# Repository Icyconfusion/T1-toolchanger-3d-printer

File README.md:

# T1-toolchanger-3d-printer
A toolchanger 3d printer with large format build size and multiple tools for quick, easy multi-material printing that uses marlin as the firmware.

**Note to reviewer:** Since submitting project for review I have updated the BOM (haven't changed products, just updated the prices). The new bom is more than what was in the review, but I have multiple discounts and coupons (that I have also tested) which bring it back down to what I mentioned in review. Thank you :) Also, in regards to firmware, the entire marlin zip folder (must be a zip) is in the firmware folder, but I have copied all files that have been edited and/or relevant (e.g config and ino files) as well into the firmware folder for the reviewer to view. I was instructed to do it this way by other reviewers in similar projects. Thanks.

I made this project as I had been looking to make a 3d printer. I wanted to be able to print in different colours, without the added cost of AMS systems. It was also a good opportunity to learn about using programs like fusion and Kicad, which I have limited experience with, as well as learning about electronic components. I created this project without a guide, using my own ideas to combat problems, with some inspiration from existing products e.g using linear rods.

Note: The assembly files are too large to upload to Github directly. Instead I have put the assembly .step file and .f3z file into a zipped folder named: Printer assembly.zip 

I have also uploaded the same step file as a zipped folder called printer assembly Step.zip, and an STL file called printer assembly STL.zip, just to be sure.

The printer uses a swappable hotend mechanism to dock tools, removing the need to purge filament as in other multi-material systems. The idle toolheads sit on an aluminium extrusion. The X carriage, supported by a V slot extrusion, moves in and attaches to the toolhead, using kinematic couplings for repeatability. A magnetic pogo connector transfers power for the heter and thermistor.

Toolhead:

# **Assembly**

The printer assembly is made by aluminium extrusions forming a cube, with corner connectors for mounting.

To support the Y axis, V slot 2020 aluminium extrusions are used as rails holding a gantry, which in turn supports the X axis.
The Y axis is made up of two carriages, one either side of the X gantry. Each Y carriage uses a gantry plate with wheels to slide along the extrusions, making the Y motion. One carriage is an idler, which the belt loops around a pulley. The other carriage is the stepper motor carriage, which uses a Nema 17 motor to drive the X axis belt. Both carriages hold 90 degree connectors supporting the X extrusion.
Idler:

Stepper carriage:

The X carriage is made of two parts: the main carriage, and the toolhead. The main carriage holds the fan and the extruder stepper motor. When the carriage comes into dock, a fixed arm pushes the extruder idle arm to the side. The filament slides into the extruder,and when docking is complete, the spring loaded, idle arm pushes back into the filament, creating good tension. 

The fan is a 4010 fan, which sits to the side and blows cool air through the heatsink fins and also onto the part/top layer. 

The belt post is located behind the carriage.

The carriage sid of the coupling contains the 6mm smooth rods of the kinematic coupling. This is printed in two pieces, so that the rods can be put into grooves before the 'lid' of the coupling closes through screws. The pogo connector is also housed here.

The toolhead uses steel balls to push into the kinematic coupling. The male side of the pogo connector is on the toolhead.

The hotend mounts to the two holes in the middle.

The Z axis involves the motion of the bed up and down. Originally, I had planned to move the hotend throughout all 3 axis, and the bed was fixed. I encountered many issues with reliably and consistently achieving motion of the hotend without the risk of flexing, so I pivoted to a bed Z axis. A leadscrew and two 8mm linear rods are used on each side, connected to an aluminium profile by a nut block and 3d printed clamps.

The bed frame is a square made of aluminium extrusions, held together by 90 degree corner connectors. The 6mm aluminium print bed sits on top of that, threaded into T nuts in the profiles.

Toolchanging mechanism. Tools are held on the toolchanger rack, installed with T nuts on an aluminium profile. L shaped hooks hold the tools in place, using knobs on the tools.Wwhen the tool slides in sideways, the knob/tool will be separated from the carriage by the hook Then the carriage will move backwards, detaching the magnets in the connectors, and pulling the tool off the rack. To attach, it simply presses the carriage onto the tool, pushes it back and slides out. The magnets used in the connector and the balls should be enough to hold the tool in place, but in the event it is not, I can use print in place function in slicers to add in even stronger magnets in the centre (only if current magnet setup isn't strong enough - unlikely).

# **Electronics**

The printer uses a PCB motherboard to mount components including the MCU (Mega 2560), stepper drivers, LCD headers, and heater terminals. I decided on a 24v power supply as it was compatible with my heater. To give power to the PCB, I used a meanwell 24v 360W power supply.

This connects through wires to screw terminals on the board, which then distribute power across the PCB. Because of the power requirements, I decided to use a 4 layer PCB as I couldn't route signal traces through the power and GND traces. Using a 4 layer PCB is necessary to the peojwct due to the power layout of drivers, making signal traces impossible without a 3rd and 4th layer. The top and bottom layers of the PCB are the power layers. Power runs from the PSU input to the heater screw terminal, and throughout the board. It is converted to 5v through a buck converter. The Hotend heater is powered through a screw terminal, and controlled by the mosfet next to its terminal. The hotend fan is controlled by a header, it is in an always on state.

The signal traces from the drivers, limit switches, thermistor and LCD are on the second and third layers.

The MCU is a mega 2560. I chose this because of its large availability of pins, enabling future upgrades and fitting all components. The stepper drivers are A4988s, which have microstepping up to 1/16. All microstep pins are connected to 5v, making the configuration 1/16. The limit switches, thermistor and lcd connect to headers.

The power for the stepper drivers is 24v. To reduce the effect of spikes, a small 100nf capacitor is used between the 24v and gnd supply of each driver. For larger spikes, a 100 uF capacitor is also placed between 24v and gnd of each driver.

The LCD is the main user interface of the printer. I am using the BIGTREETECH TFT35 V3.0 Touch Screen from BigTreeTech which has wifi capability and is 3.5". I chose this LCD as it only uses 2 pins on the MCU (TX and RX), has an SD card, and is touchscreen. It is possible to mount the LCD separately to the motherboard, and run a cable between the two, enabling you to set it up however you like. LCD Header:

The Motherboard and PSU are not fixed components to the printer and can be placed wherever suitable as long as cabling reaches. (I already have a case at home for my pcb from older projects).

### Schematic

# **Firmware**

The printer uses the latest version of marlin firmware, which enables the use of G-code. The general firmware of the printer is fairly standard and straightforward, as marlin is just configured to the printer dimensions and layout. The firmware has been edited to match the printer configuration with things like pin usage, limits, dimensions, and rough speeds/acceleration (these will require testing following assembly).

However, the printer being a toolchanger introduces a unique element to the firmware in the connection and preparation of multiple toolheads. To simplify firmware and general electronics, I decided on having 'hot-swappable' toolheads that connect through pogo connectors. Because of this, the firmware views it as one hotend when it comes to heating the temperature monitoring. In this aspect, the printer appears as standard. To facilitate toolchanges though, special G-code is required to move the carriage into specific positions. This is most effectively achieved through pre and post g-code in the slicer per tool. The main idea of the toolchange G-code is that the empty carriage moves into alignment with the passive tool, moves forward to latch on, and then returns to the print area. When returning a tool to the standby dock, it is the same idea in reverse, where it moves into a specific position, pushes the tool into the dock, and returns to pick up another tool. This is the series of G-code to paste into the slicer pre and post processing:

Pre:

M1 X(Tool X value) Y440 F6000

M1 X(Tool X value) Y480 F2000

M1 X(Tool X value + 60) Y480 F2000

M1 X(Tool X value + 60) Y440 F2000

Post:

M1 X(Tool X value + 60) Y440 F6000

M1 X(Tool X value + 60) Y480 F2000

M1 X(Tool X value) Y480 F2000

M1 X(Tool X value) Y440 F1000

The X values are unique to each tool, as tools are docked in order across the X axis. Specific values will require precise tuning with manual adjustment following assembly to ensure correct alignment of the coupling, so values are not possible now, but the spacing between docks will be roughly 100mm.

Breaking down this G-code, the carriage moves into a position hovering off of the dock, in X alignment. The carriage then slowly pushes into the docked tool in the second G-code command. At this point, the kinematic coupling engages, ensuring alignment, and the magnetic clamp and pogo connectors attach, preparing the tool for printing. The third G-code command moves the carriage and new tool to the right, out of the dock, before returning to the print area with the fourth command. this process occurs in reverse for the docking of the tool/post G-code series.

# **BOM**
### CAD

| Quanity      | Name                     |  Picture    |
| -------------| -------------------------|-----------  |
| 1            | New X carriage               |
| 1 (per tool) | Toolhead                 |
| 4            | Z axis bearing clamp     |
| 2            | Z stepper bracket        |
| 4            | Z rod holder             |
| 2       | Nema 17 parallel mount| 
|4 | plain limit switch bracket| 
|4| z rod top bracket|
|1| toolchanger rack| 

### PCB
4 layer PCB that is 230x135mm:

Layers 1 and 4 make up the power layers, 24v (a small bit of 5v) and GND. This was a requirement due to the large power draw of the machine, requiring thick traces that took up a lot of room. I tried routing the pcb using only 2 layers, but this was not possible. Layers 2 and 3 are signal layers.

### Parts

1x BTT TFT35 V3.0 LCD

1x Arduino Mega 2560

6x Limit switch

4x 8mm smooth rods, 500mm length

1x 6mm smooth rod, 500mm length

6x 8mm steel balls

15x 2020 Aluminium profile 500mm length

2x 500mm T8 8mm lead leadscrew 

2x Anti-backlash leadscrew nut

2x Hotend (CR6-SE)

1x 4010 Fan

1x GT2 Kit

2x Aluminium Profile 90 degree connector

8x Aluminium profile corner connector

1x PSU (24v 360w+)

2x Screw terminals

1x N-channel Mosfet

1x 2x18 Pin header

16x Female pin headers

42x Male pin headers

5x A4988 Stepper drivers

1x 20 AWG Wire

1x 12 AWG Wire

3x Pogo connectors

1x 3d print bed

4x LM8UU bearing

2x Angular bearing

1x DC-DC step down Buck Converter

110x T Nuts

8x L Bracket

5x 100 nF Capacitor

5x 100 µF capacitor

1x Spring

6x Leadscrew fixing block

40x M5 screws and nuts

40x M4 screws and nuts

2x Shaft coupler 5x8mm

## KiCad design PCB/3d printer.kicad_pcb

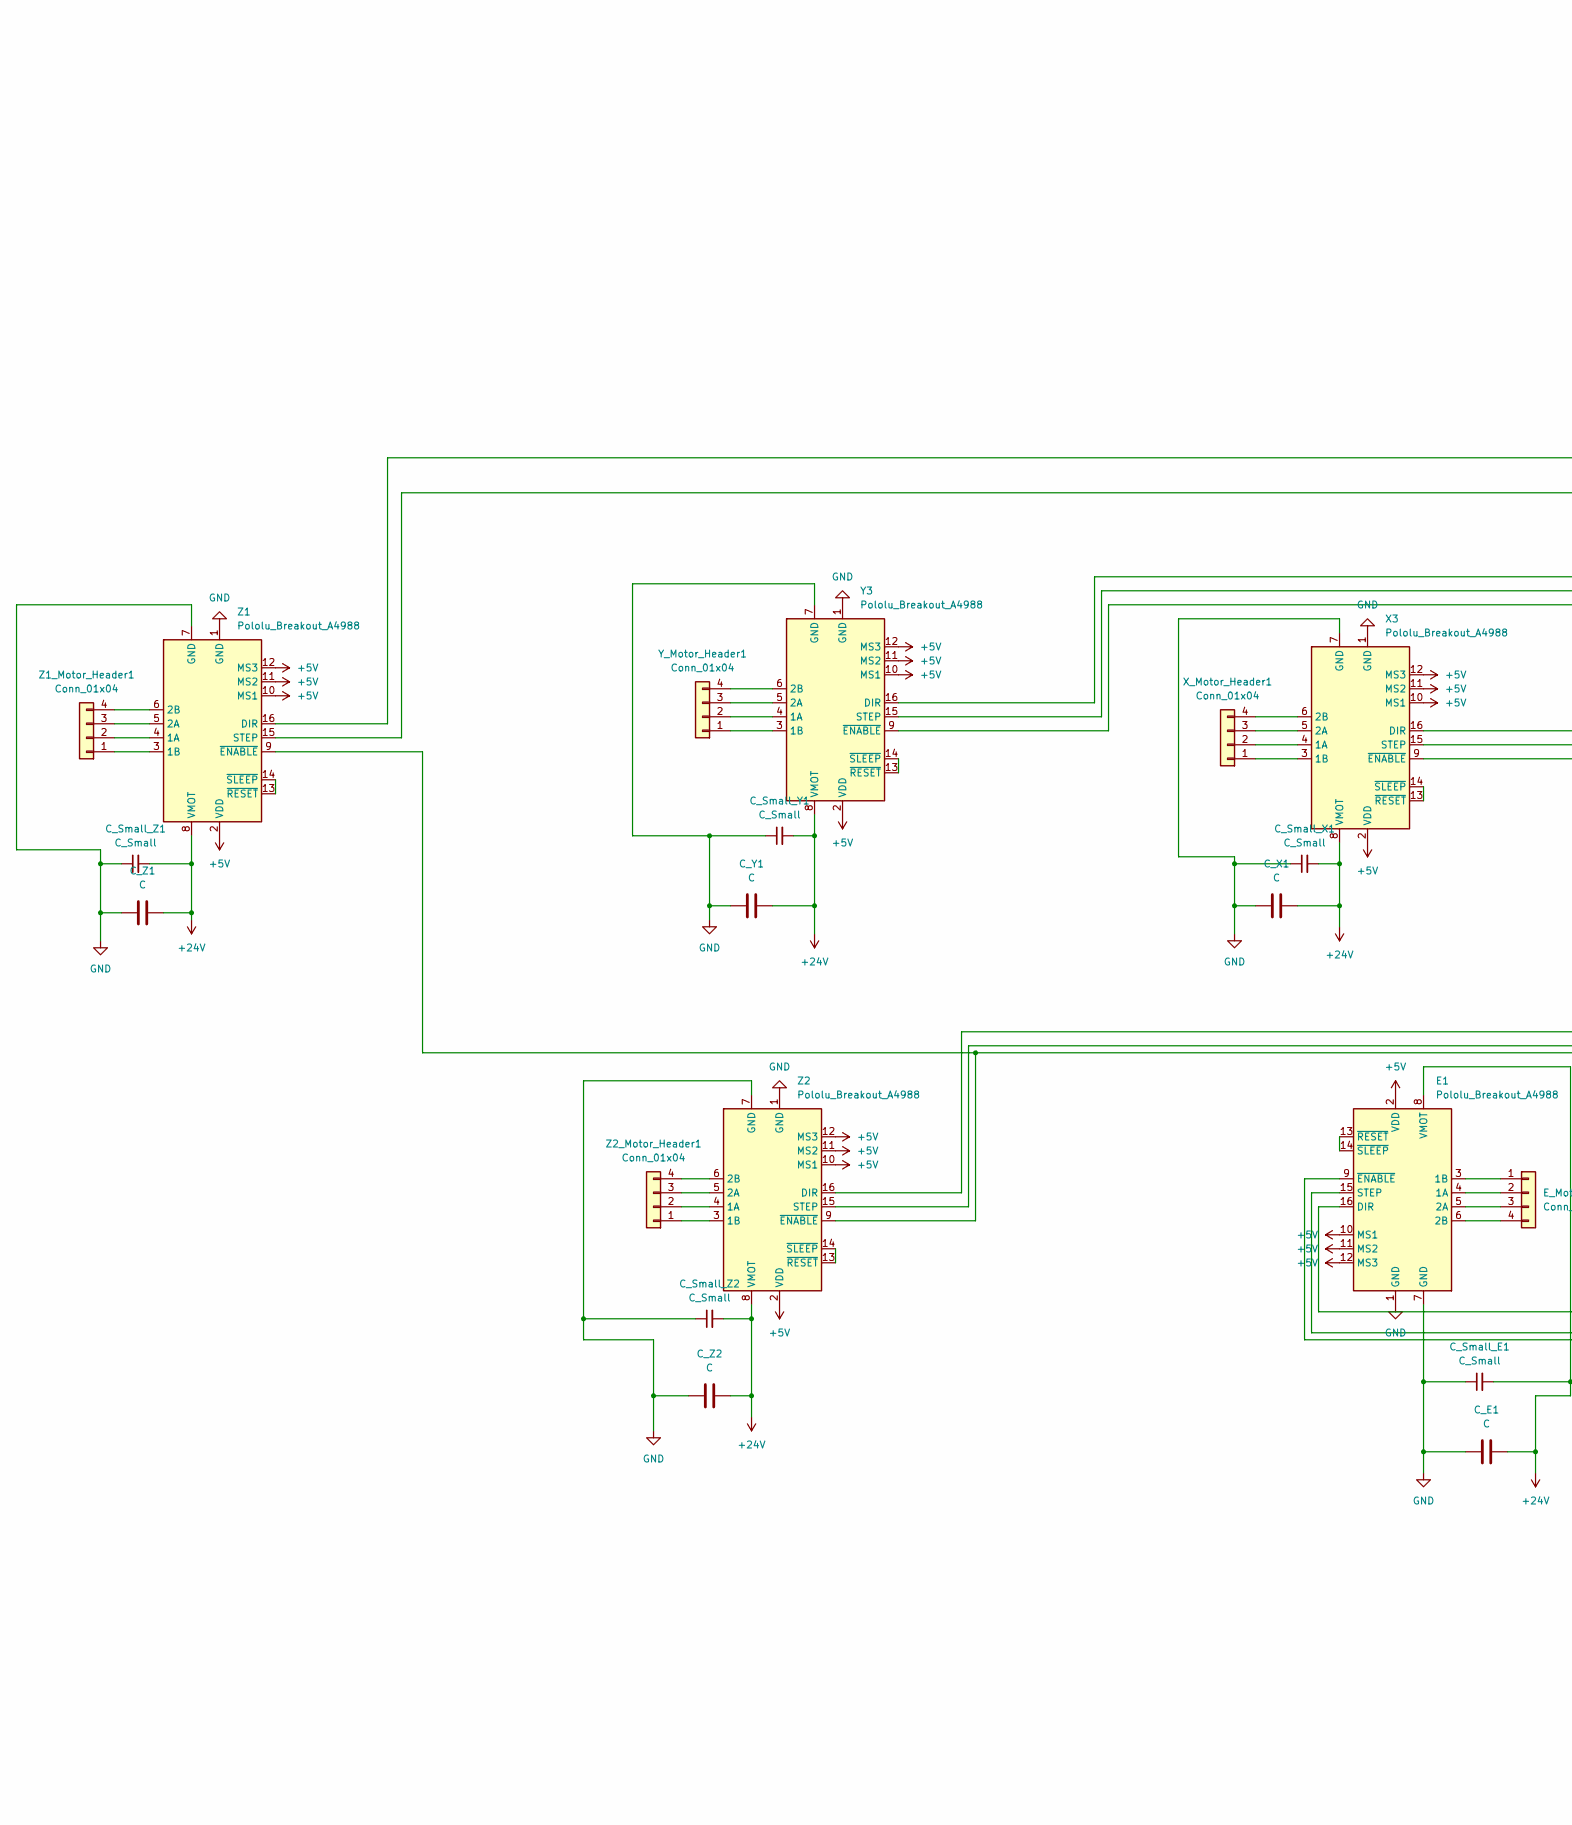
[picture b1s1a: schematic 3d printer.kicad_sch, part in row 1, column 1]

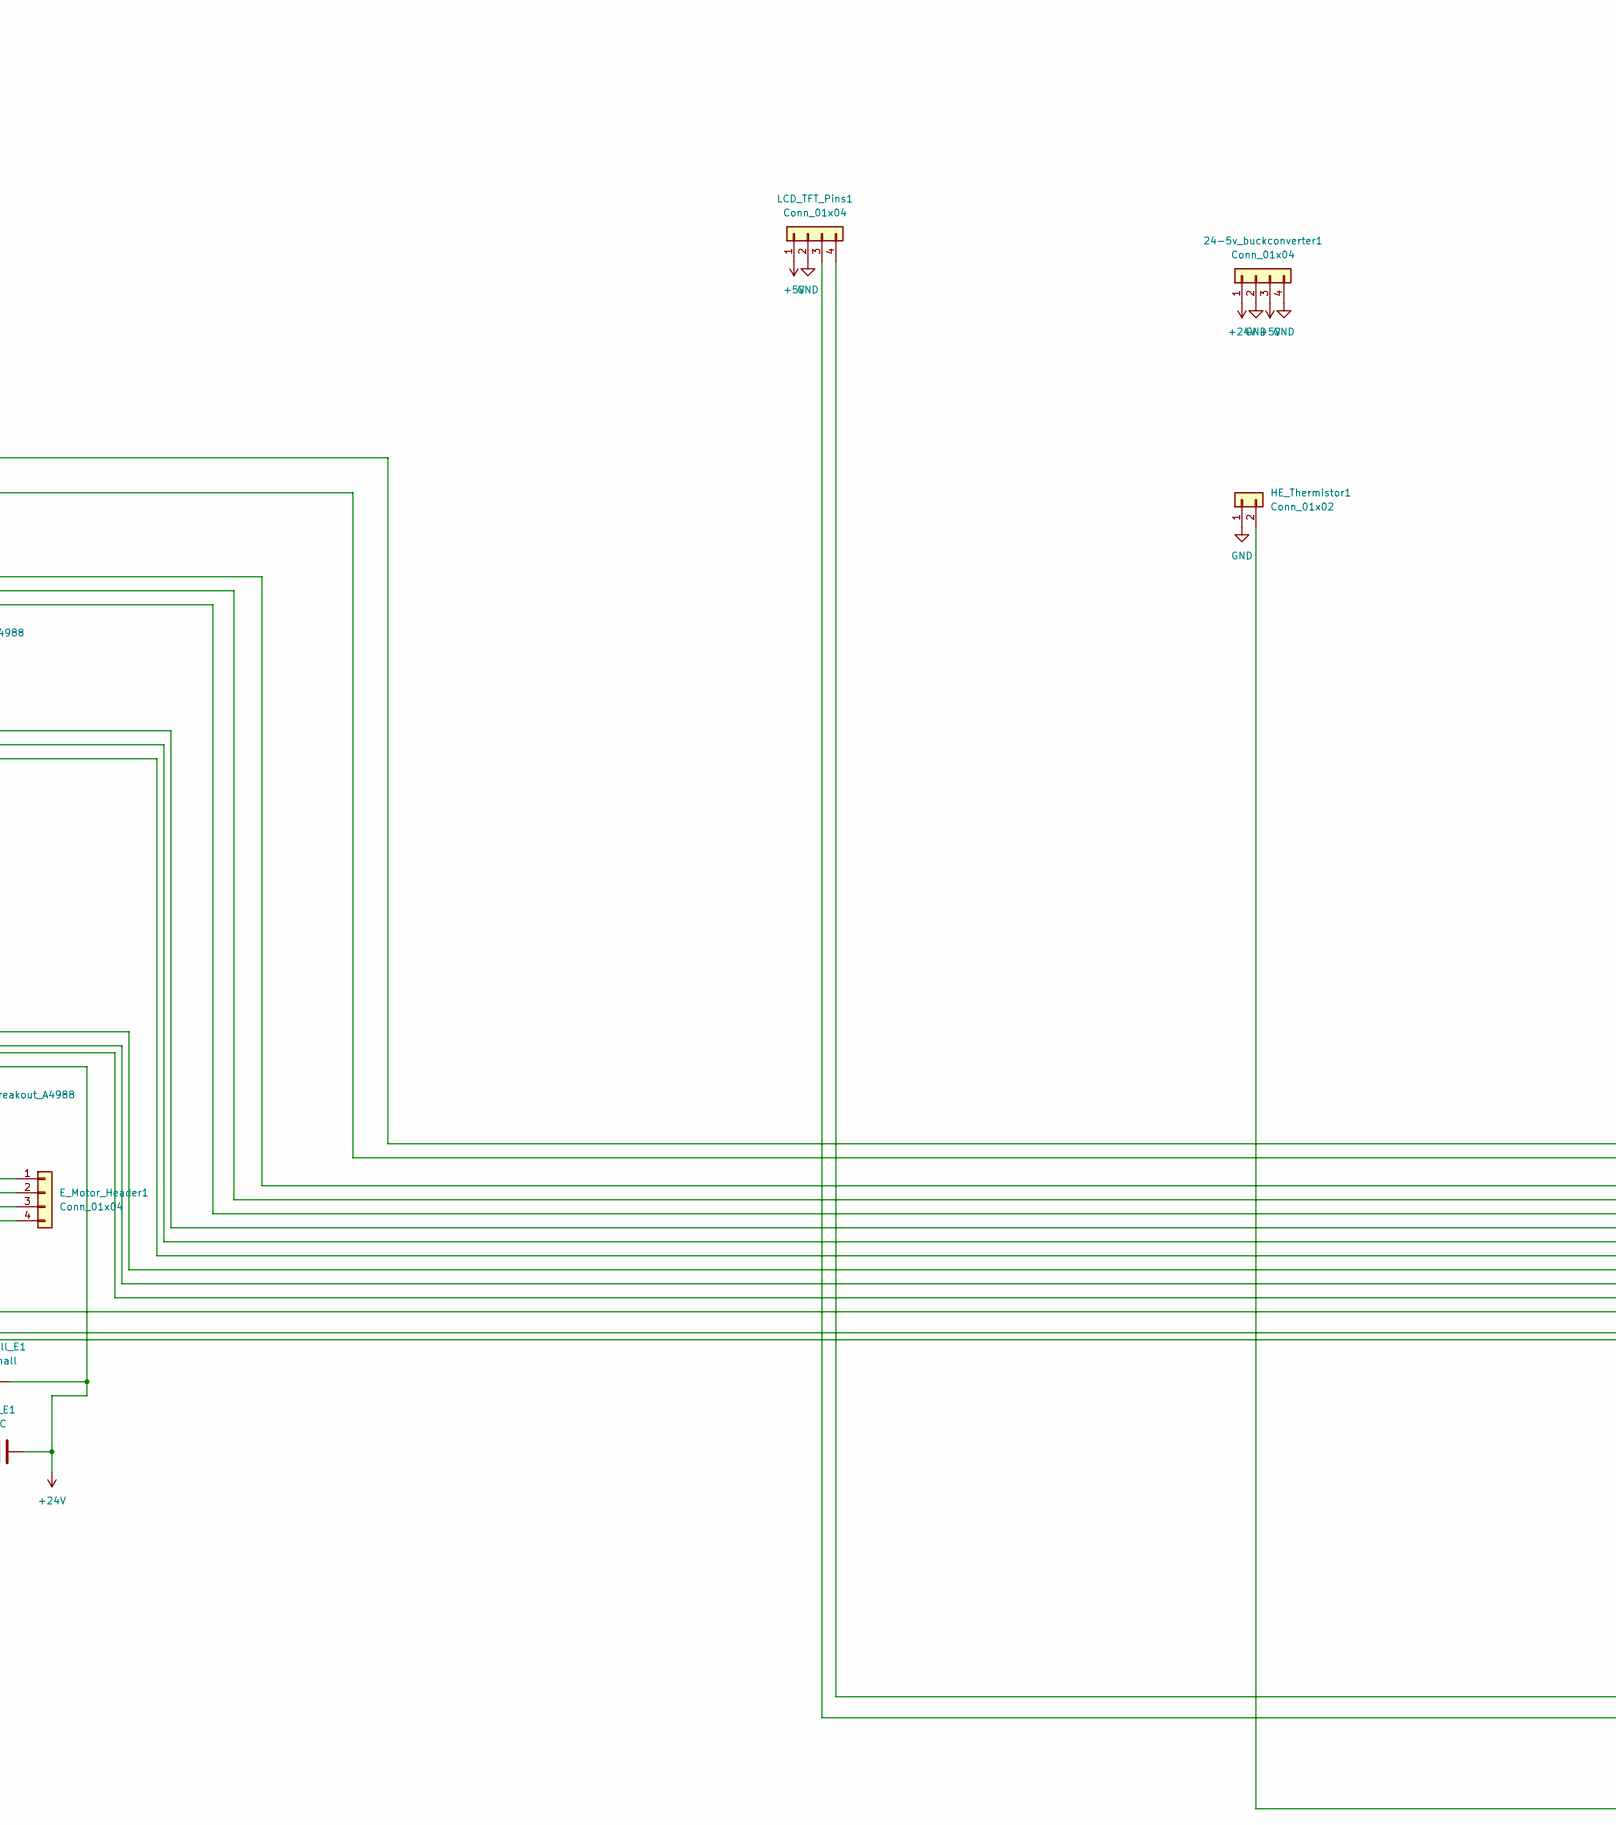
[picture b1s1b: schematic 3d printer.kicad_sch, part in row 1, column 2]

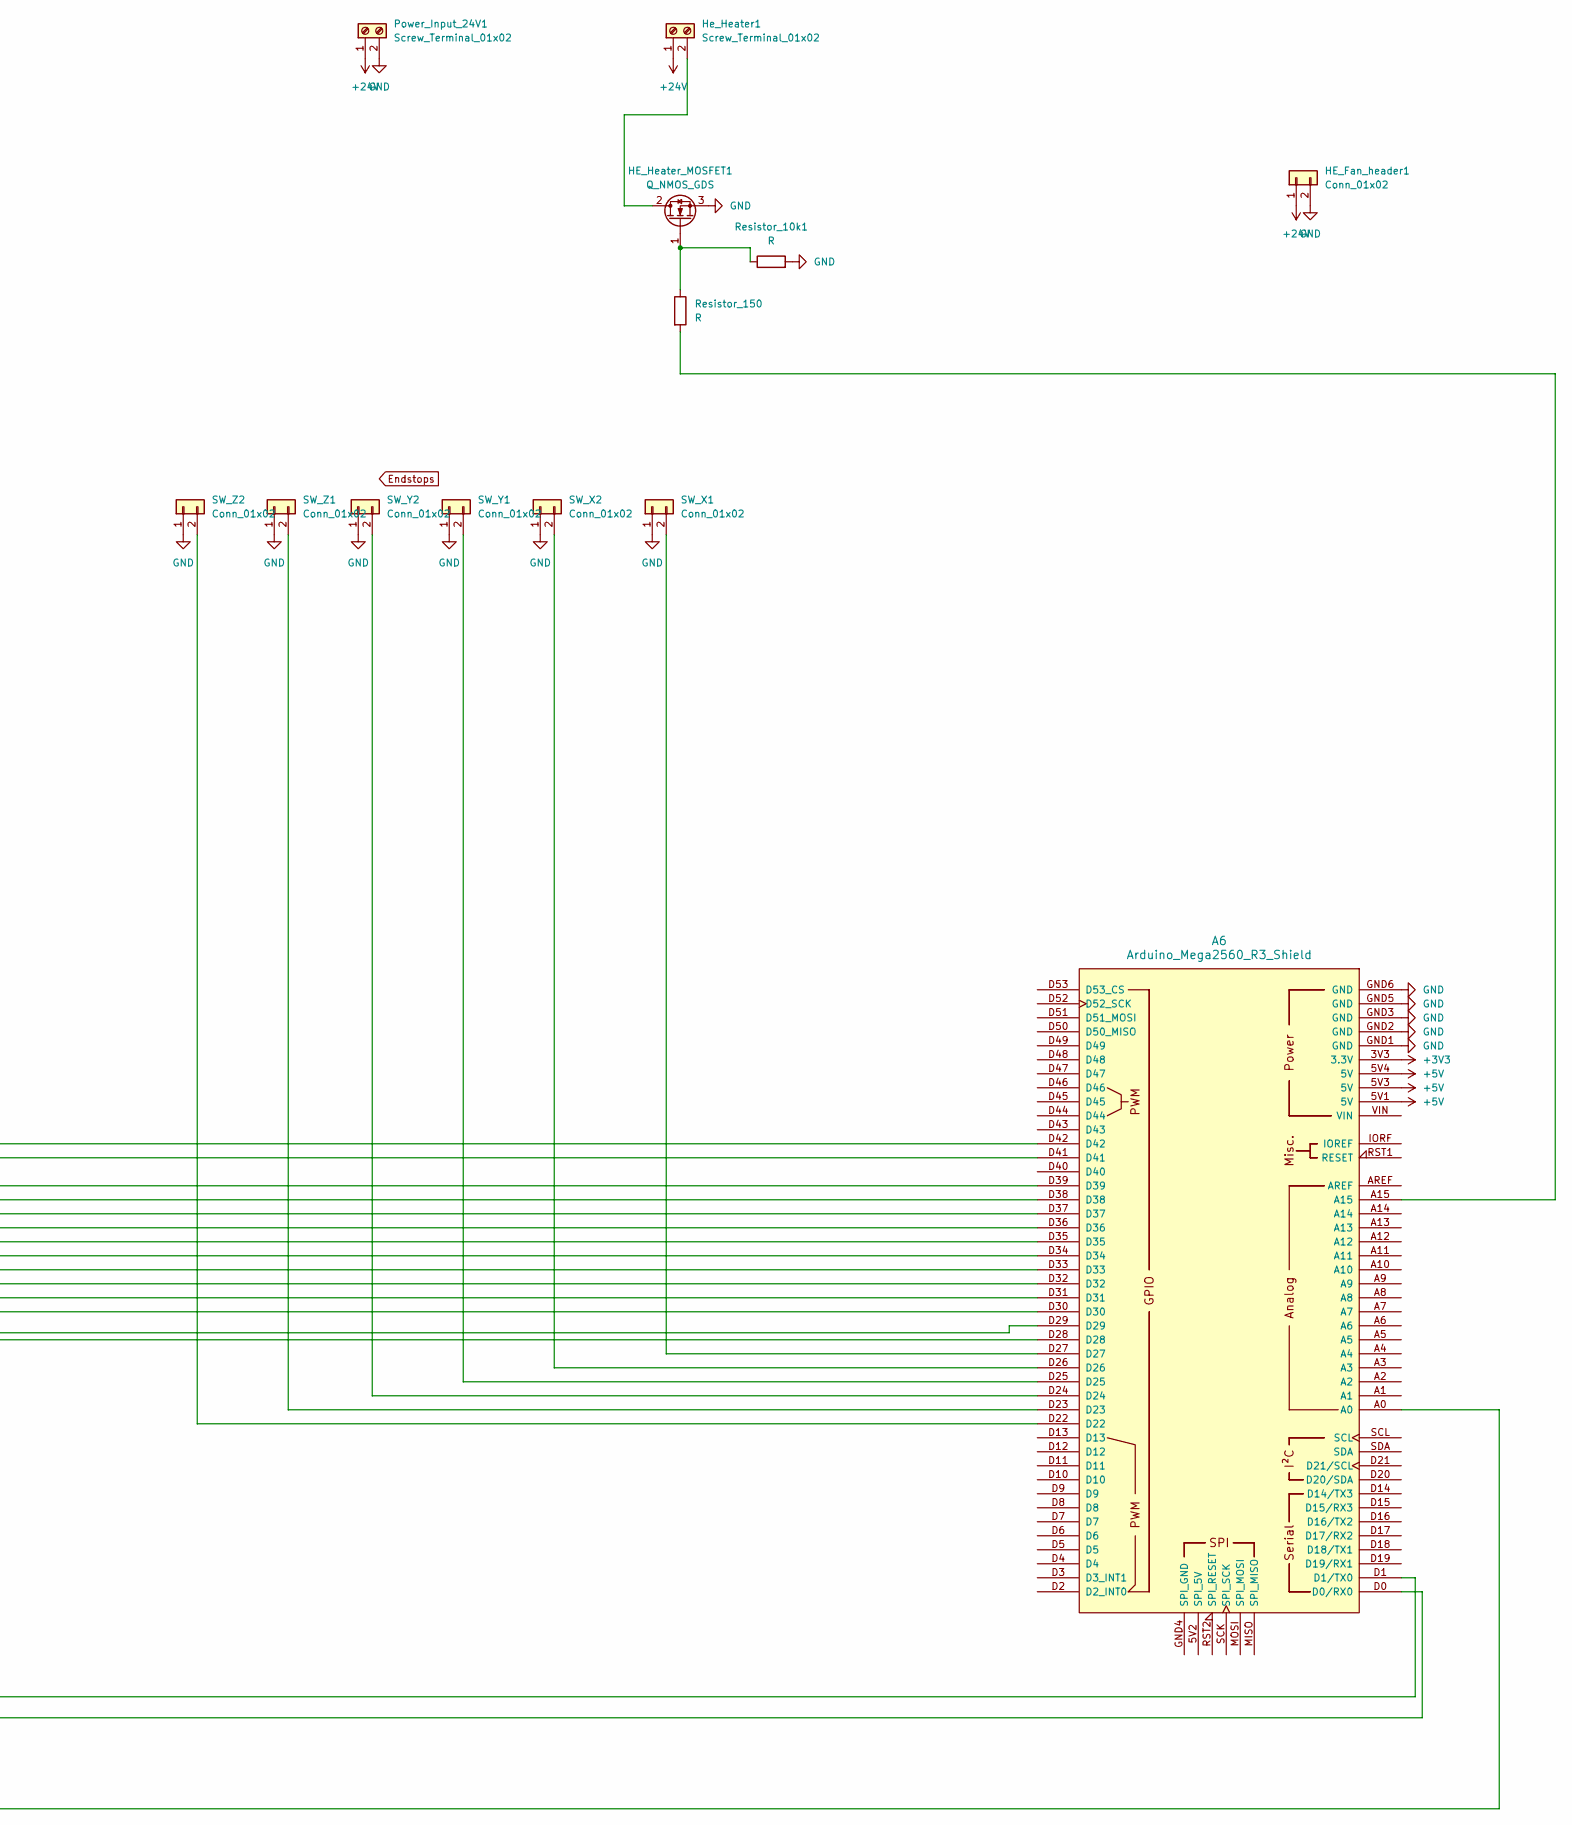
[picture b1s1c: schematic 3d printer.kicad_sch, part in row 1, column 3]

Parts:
24-5v_buckconverter1: Conn_01x04; PinHeader_1x04_P2.54mm_Vertical
A6: Arduino_Mega2560_R3_Shield
C_E1: C; CP_Radial_D8.0mm_P5.00mm
C_Small_E1: C_Small; C_Disc_D5.0mm_W2.5mm_P5.00mm
C_Small_X1: C_Small; C_Disc_D5.0mm_W2.5mm_P5.00mm
C_Small_Y1: C_Small; C_Disc_D5.0mm_W2.5mm_P5.00mm
C_Small_Z1, C_Small_Z2: C_Small; C_Disc_D5.0mm_W2.5mm_P5.00mm
C_X1: C; CP_Radial_D8.0mm_P5.00mm
C_Y1: C; CP_Radial_D8.0mm_P5.00mm
C_Z1, C_Z2: C; CP_Radial_D8.0mm_P5.00mm
E1: Pololu_Breakout_A4988; Pololu_Breakout-16_15.2x20.3mm
E_Motor_Header1: Conn_01x04; PinHeader_1x04_P2.54mm_Vertical
HE_Fan_header1: Conn_01x02; PinHeader_1x02_P2.54mm_Vertical
HE_Heater_MOSFET1: Q_NMOS_GDS; TO-220-3_Vertical
HE_Thermistor1: Conn_01x02; PinHeader_1x02_P2.54mm_Vertical
He_Heater1: Screw_Terminal_01x02; TerminalBlock_RND_205-00232_1x02_P5.08mm_Horizontal
LCD_TFT_Pins1: Conn_01x04; PinHeader_1x04_P2.54mm_Vertical
Power_Input_24V1: Screw_Terminal_01x02; TerminalBlock_RND_205-00232_1x02_P5.08mm_Horizontal
Resistor_10k1, Resistor_150: R; R_Axial_DIN0207_L6.3mm_D2.5mm_P7.62mm_Horizontal
SW_X1, SW_X2: Conn_01x02; PinHeader_1x02_P2.54mm_Vertical
SW_Y1, SW_Y2: Conn_01x02; PinHeader_1x02_P2.54mm_Vertical
SW_Z1, SW_Z2: Conn_01x02; PinHeader_1x02_P2.54mm_Vertical
X3: Pololu_Breakout_A4988; Pololu_Breakout-16_15.2x20.3mm
X_Motor_Header1: Conn_01x04; PinHeader_1x04_P2.54mm_Vertical
Y3: Pololu_Breakout_A4988; Pololu_Breakout-16_15.2x20.3mm
Y_Motor_Header1: Conn_01x04; PinHeader_1x04_P2.54mm_Vertical
Z1, Z2: Pololu_Breakout_A4988; Pololu_Breakout-16_15.2x20.3mm
Z1_Motor_Header1, Z2_Motor_Header1: Conn_01x04; PinHeader_1x04_P2.54mm_Vertical

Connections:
+3V3: A6.3V3 (3.3V)
+5V: 24-5v_buckconverter1.3, A6.5V1 (5V), A6.5V3 (5V), A6.5V4 (5V), E1.2 (VDD), E1.10 (MS1), E1.11 (MS2), E1.12 (MS3), LCD_TFT_Pins1.1, X3.2 (VDD), X3.10 (MS1), X3.11 (MS2), X3.12 (MS3), Y3.2 (VDD), Y3.10 (MS1), Y3.11 (MS2), Y3.12 (MS3), Z1.2 (VDD), Z1.10 (MS1), Z1.11 (MS2), Z1.12 (MS3), Z2.2 (VDD), Z2.10 (MS1), Z2.11 (MS2), Z2.12 (MS3)
+24V: 24-5v_buckconverter1.1, C_E1.2, C_Small_E1.2, C_Small_X1.2, C_Small_Y1.2, C_Small_Z1.2, C_Small_Z2.2, C_X1.2, C_Y1.1, C_Z1.2, C_Z2.2, E1.8 (VMOT), HE_Fan_header1.1, He_Heater1.1, Power_Input_24V1.1, X3.8 (VMOT), Y3.8 (VMOT), Z1.8 (VMOT), Z2.8 (VMOT)
GND: 24-5v_buckconverter1.2, 24-5v_buckconverter1.4, A6.GND1 (GND), A6.GND2 (GND), A6.GND3 (GND), A6.GND5 (GND), A6.GND6 (GND), C_E1.1, C_Small_E1.1, C_Small_X1.1, C_Small_Y1.1, C_Small_Z1.1, C_Small_Z2.1, C_X1.1, C_Y1.2, C_Z1.1, C_Z2.1, E1.1 (GND), E1.7 (GND), HE_Fan_header1.2, HE_Heater_MOSFET1.3 (S), HE_Thermistor1.1, LCD_TFT_Pins1.2, Power_Input_24V1.2, Resistor_10k1.2, SW_X1.1, SW_X2.1, SW_Y1.1, SW_Y2.1, SW_Z1.1, SW_Z2.1, X3.1 (GND), X3.7 (GND), Y3.1 (GND), Y3.7 (GND), Z1.1 (GND), Z1.7 (GND), Z2.1 (GND), Z2.7 (GND)
unnamed: A6.D0 (D0/RX0), LCD_TFT_Pins1.3
unnamed: A6.D1 (D1/TX0), LCD_TFT_Pins1.4
unnamed: A6.A15, Resistor_150.2
unnamed: E1.4 (1A), E_Motor_Header1.2
unnamed: E1.3 (1B), E_Motor_Header1.1
unnamed: E1.5 (2A), E_Motor_Header1.3
unnamed: E1.6 (2B), E_Motor_Header1.4
unnamed: A6.D30, E1.16 (DIR)
unnamed: A6.D29, E1.15 (STEP)
unnamed: A6.D28, E1.9 (~ENABLE)
unnamed: E1.13 (~RESET), E1.14 (~SLEEP)
unnamed: HE_Heater_MOSFET1.2 (D), He_Heater1.2
unnamed: HE_Heater_MOSFET1.1 (G), Resistor_10k1.1, Resistor_150.1
unnamed: A6.A0, HE_Thermistor1.2
unnamed: A6.D27, SW_X1.2
unnamed: A6.D26, SW_X2.2
unnamed: A6.D25, SW_Y1.2
unnamed: A6.D24, SW_Y2.2
unnamed: A6.D23, SW_Z1.2
unnamed: A6.D22, SW_Z2.2
unnamed: X3.4 (1A), X_Motor_Header1.2
unnamed: X3.3 (1B), X_Motor_Header1.1
unnamed: X3.5 (2A), X_Motor_Header1.3
unnamed: X3.6 (2B), X_Motor_Header1.4
unnamed: A6.D36, X3.16 (DIR)
unnamed: A6.D35, X3.15 (STEP)
unnamed: A6.D34, X3.9 (~ENABLE)
unnamed: X3.13 (~RESET), X3.14 (~SLEEP)
unnamed: Y3.4 (1A), Y_Motor_Header1.2
unnamed: Y3.3 (1B), Y_Motor_Header1.1
unnamed: Y3.5 (2A), Y_Motor_Header1.3
unnamed: Y3.6 (2B), Y_Motor_Header1.4
unnamed: A6.D39, Y3.16 (DIR)
unnamed: A6.D38, Y3.15 (STEP)
unnamed: A6.D37, Y3.9 (~ENABLE)
unnamed: Y3.13 (~RESET), Y3.14 (~SLEEP)
unnamed: Z1.4 (1A), Z1_Motor_Header1.2
unnamed: Z1.3 (1B), Z1_Motor_Header1.1
unnamed: Z1.5 (2A), Z1_Motor_Header1.3
unnamed: Z1.6 (2B), Z1_Motor_Header1.4
unnamed: A6.D42, Z1.16 (DIR)
unnamed: A6.D41, Z1.15 (STEP)
unnamed: A6.D31, Z1.9 (~ENABLE), Z2.9 (~ENABLE)
unnamed: Z1.13 (~RESET), Z1.14 (~SLEEP)
unnamed: Z2.4 (1A), Z2_Motor_Header1.2
unnamed: Z2.3 (1B), Z2_Motor_Header1.1
unnamed: Z2.5 (2A), Z2_Motor_Header1.3
unnamed: Z2.6 (2B), Z2_Motor_Header1.4
unnamed: A6.D33, Z2.16 (DIR)
unnamed: A6.D32, Z2.15 (STEP)
unnamed: Z2.13 (~RESET), Z2.14 (~SLEEP)

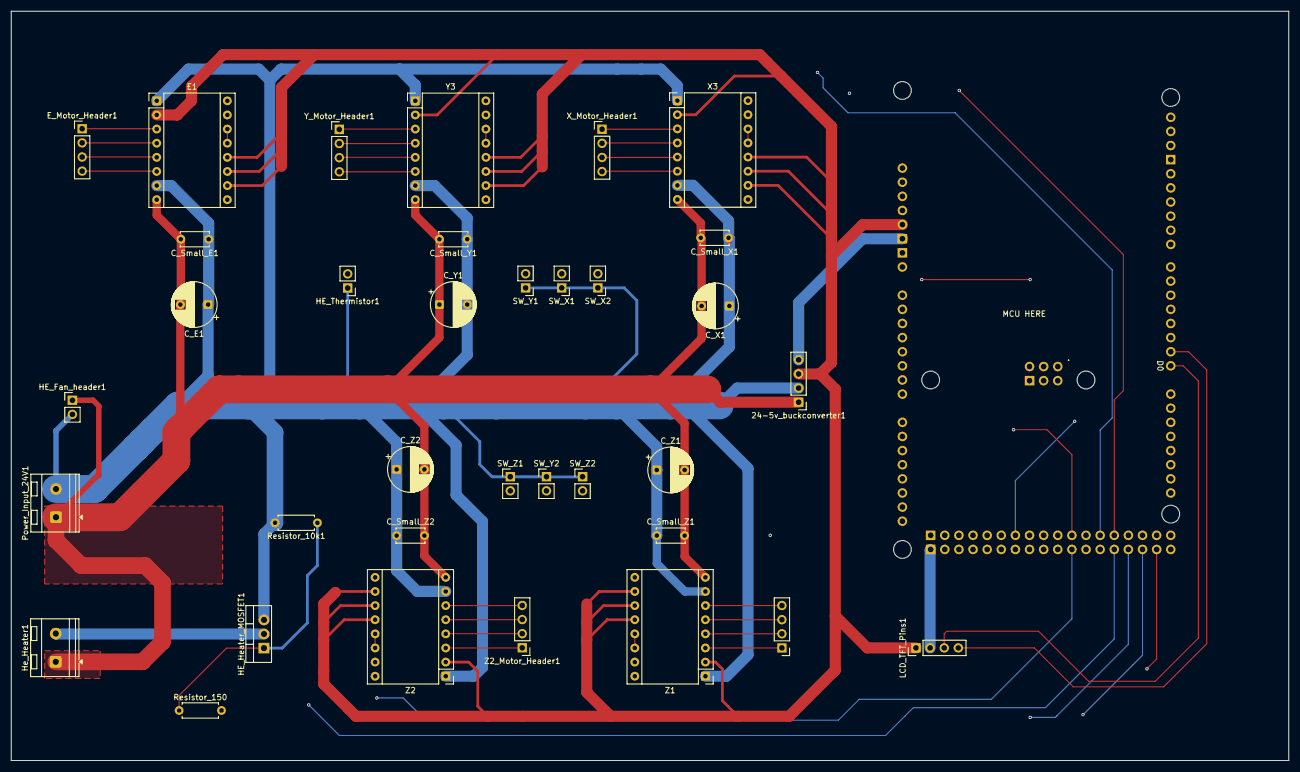
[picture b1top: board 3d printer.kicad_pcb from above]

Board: 4 copper layers, 229.8 x 134.8 mm, 36 parts (0 on the bottom side), 54 nets.

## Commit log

2025-12-29 Added BOM
2026-01-05 Rename 3d printer.kicad_prl to PCB/3d printer.kicad_prl
2026-01-05 Rename 3d printer.kicad_pro to PCB/3d printer.kicad_pro
2026-01-05 Rename Complete printer assembly.f3z to Assembly/Complete printer assembly.f3z
2026-01-05 Rename Complete printer assembly.step to Assembly/Complete printer assembly.step
2026-01-05 Rename Complete printer assembly.zip to Assembly/Complete printer assembly.zip
2026-01-05 Rename Marlin-2.1.2.6.zip to Firmware/Marlin-2.1.2.6.zip
2026-02-18 Rename Printer assembly step.zip to CAD/Printer assembly step.zip
